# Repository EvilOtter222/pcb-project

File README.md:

# RP2040 Switch Inspired Console
A nintendo switch inspired handheld game console I designed in KiCad, built around a bare RP2040 chip.

## About
Hi, I'm Kai (or `@relufied`), a 9th grader from New Jersey passionate about all things electronics and machine learning! 

This is my first PCB ever. I've done a lot of embedded stuff before (Arduino, Picos, ESP chips) and I built an 8-bit breadboard computer, but everything I've made was on breadboards and protoboards. I had never opened PCB software before this.

The idea came from a handheld I made with an ESP32 and a capacitive touch TFT (my reddit post a year ago: https://www.reddit.com/r/arduino/comments/1r4qdw3/breakout_game_with_tft_and_arduino/). I wanted to build something like that again, but with everything on one board, so the RP2040 goes straight on the PCB. I picked the RP2040 because it's cheap, it's fast-ish, and I've used it a bunch.

Made for Hack Club Half Life (week 1).

## Features

- RP2040 with 16MB of flash (W25Q128) and a 12MHz crystal
- 2.0" 240x320 IPS display (ST7789, SPI) on a 14 pin ribbon connector
- 8 buttons for controls, plus boot and reset buttons
- Joy-Con style analog thumbstick
- Speaker with a PAM8302A amp (PWM audio)
- USB-C for power and programming (no battery)
- 3 pin debug header in case USB doesn't work on my first board
- 6 pin expansion header with serial and I2C for add-ons later, like a gyro
- 110 x 60mm, 2 layer board with a ground fill on both sides

## Pictures

| Front | Back |
|---|---|
|  |  |

PCB:

Schematic:

All the SMD parts are on the back and the front only has the buttons. There's a slot cut in the board so the display ribbon can go through to its connector on the back.

## How it works

**Power:** USB-C gives 5V and an AP2112K regulator turns it into 3.3V for the chip, flash and display. The 5.1k resistors on the CC pins make chargers see the board as a device.

**Display:** SPI on GPIO17 to GPIO21. The backlight runs off 5V through a 47 ohm resistor and an NPN transistor, switched by GPIO22.

**Buttons:** Each one connects its pin to ground, and the firmware uses the RP2040's internal pull-ups.

**Thumbstick:** The stick has no datasheet, so all 4 outer ribbon pins go to GPIO26 to GPIO29 (the ADC pins) through 330 ohm resistors. The code picks which ones are power, ground, X and Y. The click goes to GPIO10. The code I gave you might not work the first time, so try swapping the order of the pins. 

**Sound:** GPIO15 makes a PWM signal, a 10k/1k divider shrinks it, and a 22nF cap filters it before it goes into the PAM8302A. GPIO14 turns the amp on.
## Firmware

The test code is in `firmware/firmware.ino`. It's Arduino code using the Earle Philhower RP2040 core and the Adafruit ST7789 library.

It's a short and simple sanity test tests. it turns on the screen and backlight, shows which buttons are pressed, shows the thumbstick X and Y values, beeps the speaker at startup and when the stick is clicked, and sends a message out to the expansion header.

The board isn't built yet, so the code hasn't been tested. The comments will explain how to use and implement the code for each of these features. 
## Pin map

| Pin | What it does |
|---|---|
| GPIO0, GPIO1 | Expansion header (serial) |
| GPIO2 to GPIO9 | The 8 buttons |
| GPIO10 | Thumbstick click |
| GPIO12, GPIO13 | Expansion I2C |
| GPIO14 | Amp on/off |
| GPIO15 | Audio (PWM) |
| GPIO17 to GPIO21 | Display (SPI) |
| GPIO22 | Backlight |
| GPIO26 to GPIO29 | Thumbstick |
| SWCLK, SWDIO | Debug header |

## Files

- `pcb-project.kicad_sch`: schematic
- `pcb-project.kicad_pcb`: PCB
- `gerbers/` and `gerbers.zip`: files to send to JLCPCB
- `firmware/`: code
- `bom.csv` and `BOM.md`: parts list
- `JOURNAL.md`: my journal (synced from Half Life)

## BOM

The full list is in `BOM.md` and `bom.csv`. Parts are about $29, and about $64 with tax and shipping (estimated). The board is from JLCPCB and the parts are from LCSC, Mouser and BuyDisplay. I already had the thumbstick and speaker.

## Building it
1. Order the board from JLCPCB with `gerbers.zip` (default settings, 2 layers, tented vias)
2. Solder the SMD parts on the back. There are pads under for hotplate use. 
3. Solder the buttons, headers and speaker connector with an iron.
4. Put the display ribbon through the slot, then plug in the thumbstick and speaker.
5. Hold BOOT, plug in USB-C, and drag the firmware onto the drive that shows up.

## Future plans!

The design is done. DRC shows 0 unconnected items, and 2 cosmetic errors. I did this last minute but if I had more time I would use a 40 pin tft instead of a 14 pin one. 

## What I learned

1. KiCad from scratch: schematic, footprints, ERC, placement, routing, DRC and gerbers
2. Everything a bare RP2040 needs to boot: flash, crystal, decoupling caps and USB resistors
3. How vias actually work (they're holes in the board, not as simple as a color swap)
4. The autorouter is a scam. I used Freerouting to speed things up (and got the okay by `@Shadow` in even though it's normally not allowed in the Half Life huddle), but it left 27 connections it couldn't do and a mess of vias and pins that were surround by layers and layers of wires :( . I routed all 27 connections of those by hand, and next time I'm routing everything by hand.
5. Time management (how to cram 16 hours of development in the span of 3 days)

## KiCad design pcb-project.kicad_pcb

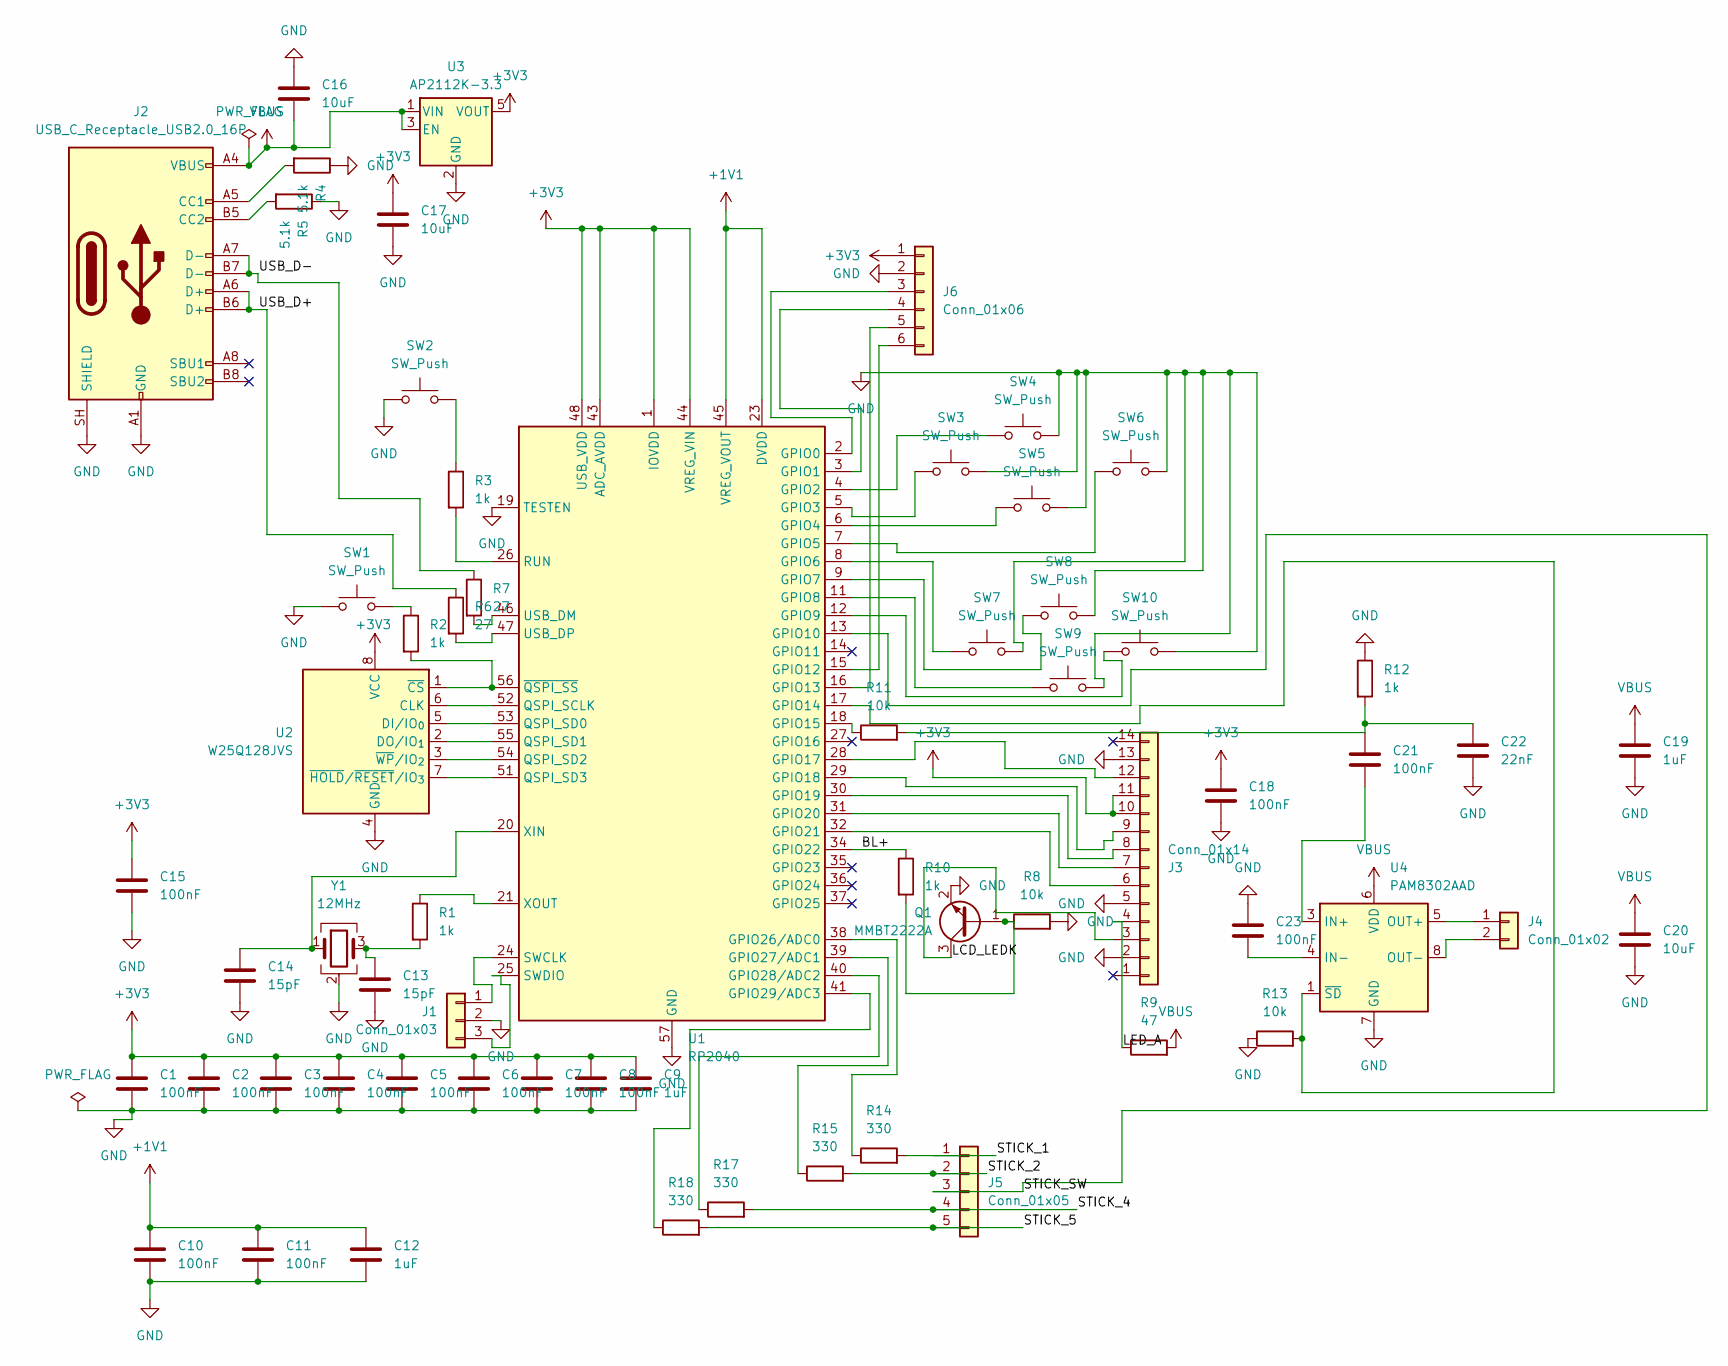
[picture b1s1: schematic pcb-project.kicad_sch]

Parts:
C1, C2, C3, C4, C5, C6, C7, C8, C10, C11, C15, C18, C21, C23: 100nF; C_0603_1608Metric
C9, C12, C19: 1uF; C_0603_1608Metric
C13, C14: 15pF; C_0603_1608Metric
C16, C17, C20: 10uF; C_0805_2012Metric
C22: 22nF; C_0603_1608Metric
J1: Conn_01x03; PinHeader_1x03_P2.54mm_Vertical
J2: USB_C_Receptacle_USB2.0_16P; USB_C_Receptacle_HRO_TYPE-C-31-M-12
J3: Conn_01x14; Hirose_FH12-14S-0.5SH_1x14-1MP_P0.50mm_Horizontal
J4: Conn_01x02; JST_PH_B2B-PH-K_1x02_P2.00mm_Vertical
J5: Conn_01x05; TE_0-1734839-5_1x05-1MP_P0.5mm_Horizontal
J6: Conn_01x06; PinHeader_1x06_P2.54mm_Vertical
Q1: MMBT2222A; SOT-23
R1, R2, R3, R10, R12: 1k; R_0603_1608Metric
R4, R5: 5.1k; R_0603_1608Metric
R6, R7: 27; R_0603_1608Metric
R8, R11, R13: 10k; R_0603_1608Metric
R9: 47; R_0805_2012Metric
R14, R15, R17, R18: 330; R_0603_1608Metric
SW1, SW2, SW3, SW4, SW5, SW6, SW7, SW8, SW9, SW10: SW_Push; SW_PUSH_6mm
U1: RP2040; QFN-56-1EP_7x7mm_P0.4mm_EP3.2x3.2mm
U2: W25Q128JVS; SOIC-8_5.3x5.3mm_P1.27mm
U3: AP2112K-3.3; SOT-23-5
U4: PAM8302AAD; SOIC-8_3.9x4.9mm_P1.27mm
Y1: 12MHz; Crystal_SMD_Abracon_ABM8G-4Pin_3.2x2.5mm

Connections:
+1V1: C10.1, C11.1, C12.1, U1.23 (DVDD), U1.45 (VREG_VOUT), U1.50 (DVDD)
+3V3: C1.1, C2.1, C3.1, C4.1, C5.1, C6.1, C7.1, C8.1, C9.1, C15.1, C17.1, C18.1, J3.10, J3.11, J6.1, U1.1 (IOVDD), U1.10 (IOVDD), U1.22 (IOVDD), U1.33 (IOVDD), U1.42 (IOVDD), U1.43 (ADC_AVDD), U1.44 (VREG_VIN), U1.48 (USB_VDD), U1.49 (IOVDD), U2.8 (VCC), U3.5 (VOUT)
/BL+: R10.1, U1.34 (GPIO22)
/LCD_LEDK: J3.3, Q1.3 (C)
/LED_A: J3.4, R9.1
/STICK_1: J5.1, R14.2
/STICK_2: J5.2, R15.2
/STICK_4: J5.4, R17.2
/STICK_5: J5.5, R18.2
/STICK_SW: J5.3, U1.13 (GPIO10)
/USB_D+: J2.A6 (D+), J2.B6 (D+), R6.1
/USB_D-: J2.A7 (D-), J2.B7 (D-), R7.1
GND: C1.2, C2.2, C3.2, C4.2, C5.2, C6.2, C7.2, C8.2, C9.2, C10.2, C11.2, C12.2, C13.2, C14.2, C15.2, C16.1, C17.2, C18.2, C19.2, C20.2, C22.2, C23.2, J1.2, J2.A1 (GND), J2.A12 (GND), J2.B1 (GND), J2.B12 (GND), J2.SH (SHIELD), J3.2, J3.5, J3.13, J6.2, Q1.2 (E), R4.1, R5.1, R8.2, R12.1, R13.1, SW1.1, SW2.1, SW3.2, SW4.2, SW5.2, SW6.2, SW7.2, SW8.2, SW9.2, SW10.2, U1.19 (TESTEN), U1.57 (GND), U2.4 (GND), U3.2 (GND), U4.7 (GND), Y1.2 (G), Y1.4 (G)
unnamed: C13.1, R1.2, Y1.3
unnamed: C21.1, C22.1, R11.2, R12.2
unnamed: J1.1, U1.24 (SWCLK)
unnamed: J1.3, U1.25 (SWDIO)
unnamed: J2.A5 (CC1), R4.2
unnamed: J2.B5 (CC2), R5.2
unnamed: J3.6, U1.32 (GPIO21)
unnamed: J3.7, U1.31 (GPIO20)
unnamed: J3.8, U1.30 (GPIO19)
unnamed: J3.9, U1.29 (GPIO18)
unnamed: J3.12, U1.28 (GPIO17)
unnamed: J4.1, U4.5 (OUT+)
unnamed: J4.2, U4.8 (OUT-)
unnamed: J6.3, U1.2 (GPIO0)
unnamed: J6.4, U1.3 (GPIO1)
unnamed: J6.5, U1.16 (GPIO13)
unnamed: J6.6, U1.15 (GPIO12)
unnamed: Q1.1 (B), R8.1, R10.2
unnamed: R2.1, SW1.2
unnamed: R3.1, SW2.2
unnamed: SW4.1, U1.4 (GPIO2)
unnamed: SW3.1, U1.5 (GPIO3)
unnamed: SW5.1, U1.6 (GPIO4)
unnamed: SW6.1, U1.7 (GPIO5)
unnamed: SW7.1, U1.8 (GPIO6)
unnamed: SW8.1, U1.9 (GPIO7)
unnamed: SW9.1, U1.11 (GPIO8)
unnamed: SW10.1, U1.12 (GPIO9)
unnamed: R13.2, U1.17 (GPIO14), U4.1 (~SD)
unnamed: R11.1, U1.18 (GPIO15)
unnamed: R14.1, U1.38 (GPIO26/ADC0)
unnamed: R15.1, U1.39 (GPIO27/ADC1)
unnamed: R17.1, U1.40 (GPIO28/ADC2)
unnamed: R18.1, U1.41 (GPIO29/ADC3)
unnamed: U1.52 (QSPI_SCLK), U2.6 (CLK)
unnamed: U1.53 (QSPI_SD0), U2.5 (DI/IO_{0})
unnamed: U1.55 (QSPI_SD1), U2.2 (DO/IO_{1})
unnamed: U1.54 (QSPI_SD2), U2.3 (~WP/IO_{2})
unnamed: U1.51 (QSPI_SD3), U2.7 (~HOLD/~RESET/IO_{3})
unnamed: R3.2, U1.26 (RUN)
unnamed: R7.2, U1.46 (USB_DM)
unnamed: R6.2, U1.47 (USB_DP)
unnamed: C14.1, U1.20 (XIN), Y1.1
unnamed: R1.1, U1.21 (XOUT)
unnamed: R2.2, U1.56 (~QSPI_SS), U2.1 (~CS)
unnamed: C21.2, U4.3 (IN+)
unnamed: C23.1, U4.4 (IN-)
VBUS: C16.2, C19.1, C20.1, J2.A4 (VBUS), J2.A9 (VBUS), J2.B4 (VBUS), J2.B9 (VBUS), R9.2, U3.1 (VIN), U3.3 (EN), U4.6 (VDD)

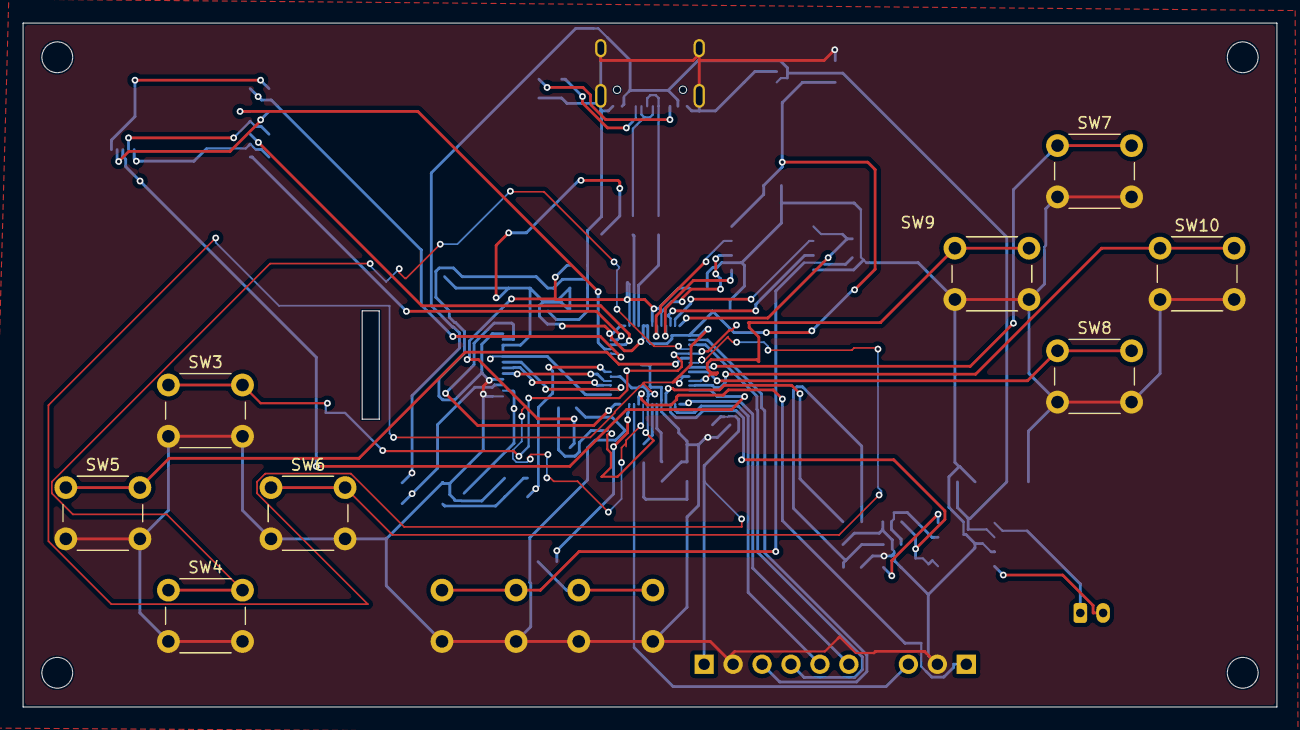
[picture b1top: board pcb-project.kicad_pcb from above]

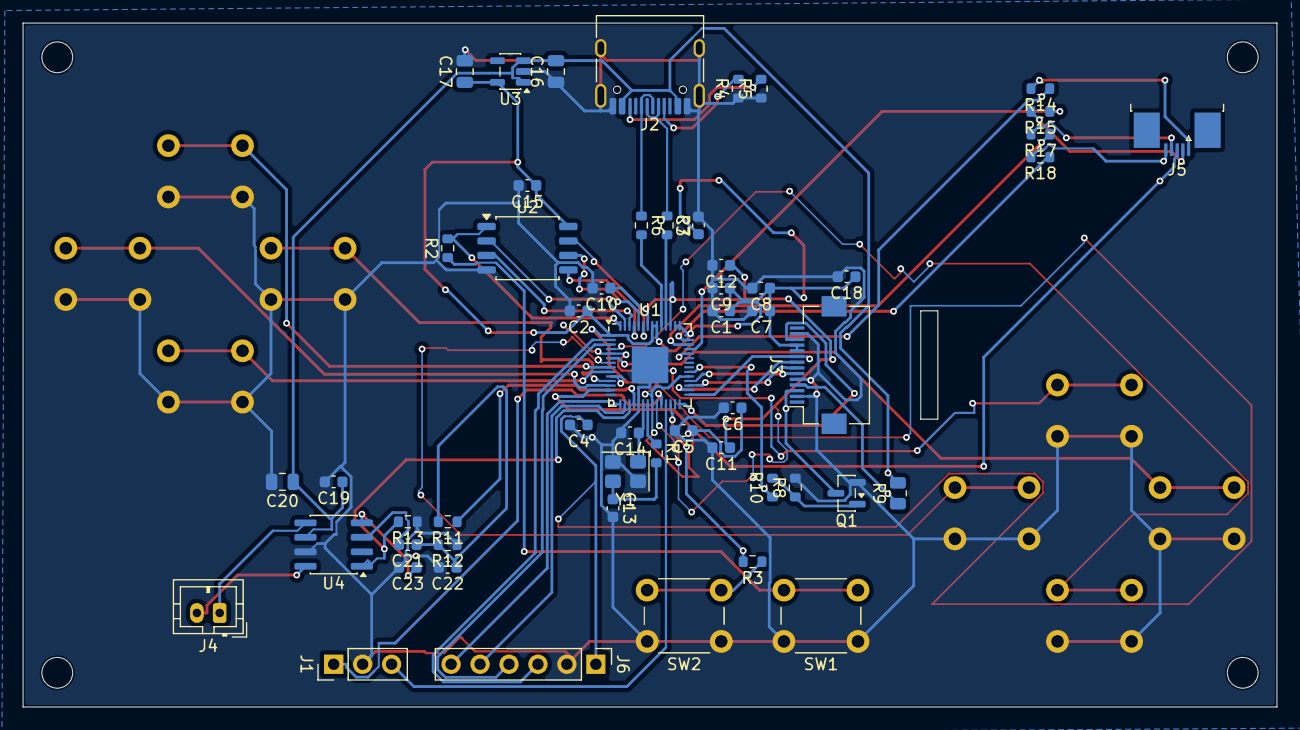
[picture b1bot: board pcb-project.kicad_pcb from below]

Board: 2 copper layers, 110.0 x 60.0 mm, 62 parts (54 on the bottom side), 61 nets.

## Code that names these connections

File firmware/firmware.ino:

// RP2040 Chip - test code
// Board: Use the Raspberry Pi Pico, this tells arduino ide to use the Earle Philhower RP2040 core
// Libraries: Adafruit GFX, Adafruit ST7735 and ST7789
//
// Tests each part, it's for YOU to make the actual games and fun stuff!
#include <Adafruit_GFX.h>
#include <Adafruit_ST7789.h>
#include <SPI.h>

// display (SPI0, SCK = 18, MOSI = 19)
#define TFT_CS    17
#define TFT_DC    20
#define TFT_RST   21
#define BACKLIGHT 22

// sound
#define AMP_ON  14
#define SPEAKER 15

// thumbstick
#define STICK_VCC   26
#define STICK_X     27
#define STICK_Y     28
#define STICK_GND   29
#define STICK_CLICK 10

// the 8 buttons are on GPIO2 to GPIO9
int buttons[8] = {2, 3, 4, 5, 6, 7, 8, 9};

Adafruit_ST7789 tft = Adafruit_ST7789(TFT_CS, TFT_DC, TFT_RST);

void setup() {
  Serial.begin(115200);  // USB
  Serial1.begin(9600);   // expansion header (TX = GPIO0, RX = GPIO1). add your own modules, like a gyro, gps, etc. 
  // buttons connect to ground, so use the pull-ups
  for (int i = 0; i < 8; i++) {
    pinMode(buttons[i], INPUT_PULLUP);
  }
  pinMode(STICK_CLICK, INPUT_PULLUP);
  // two pins are used as power and ground
  // swap them around if they don't work, not sure if this will work. 
  pinMode(STICK_VCC, OUTPUT);
  digitalWrite(STICK_VCC, HIGH);
  pinMode(STICK_GND, OUTPUT);
  digitalWrite(STICK_GND, LOW);

  // backlight for the tft
  pinMode(BACKLIGHT, OUTPUT);
  digitalWrite(BACKLIGHT, HIGH);

  // screen
  tft.init(240, 320);
  tft.setRotation(1);
  tft.fillScreen(ST77XX_BLACK);
  tft.setTextColor(ST77XX_WHITE, ST77XX_BLACK);
  tft.setTextSize(2);
  tft.setCursor(10, 10);
  tft.println("RP2040 Chip");

  // turn the amp on and play a startup beep
  pinMode(AMP_ON, OUTPUT);
  digitalWrite(AMP_ON, HIGH);
  tone(SPEAKER, 880, 200);

  Serial1.println("hello from the expansion header");
}

void loop() {
  // buttons: 1 = pressed
  tft.setCursor(10, 50);
  tft.print("Buttons: ");
  for (int i = 0; i < 8; i++) {
    if (digitalRead(buttons[i]) == LOW) {
      tft.print("1");
    } else {
      tft.print("0");
    }
  }

  // thumbstick
  int x = analogRead(STICK_X);
  int y = analogRead(STICK_Y);

  tft.setCursor(10, 80);
  tft.print("X: ");
  tft.print(x);
  tft.print("    ");  // clears old digits

  tft.setCursor(10, 110);
  tft.print("Y: ");
  tft.print(y);
  tft.print("    ");

  // beep when the stick is clicked
  if (digitalRead(STICK_CLICK) == LOW) {
    tone(SPEAKER, 440, 100);
  }

  // also print the stick to the computer
  Serial.print(x);
  Serial.print(" ");
  Serial.println(y);

  delay(50);
}

// NOW GO MAKE YOUR OWN GAMES!!
